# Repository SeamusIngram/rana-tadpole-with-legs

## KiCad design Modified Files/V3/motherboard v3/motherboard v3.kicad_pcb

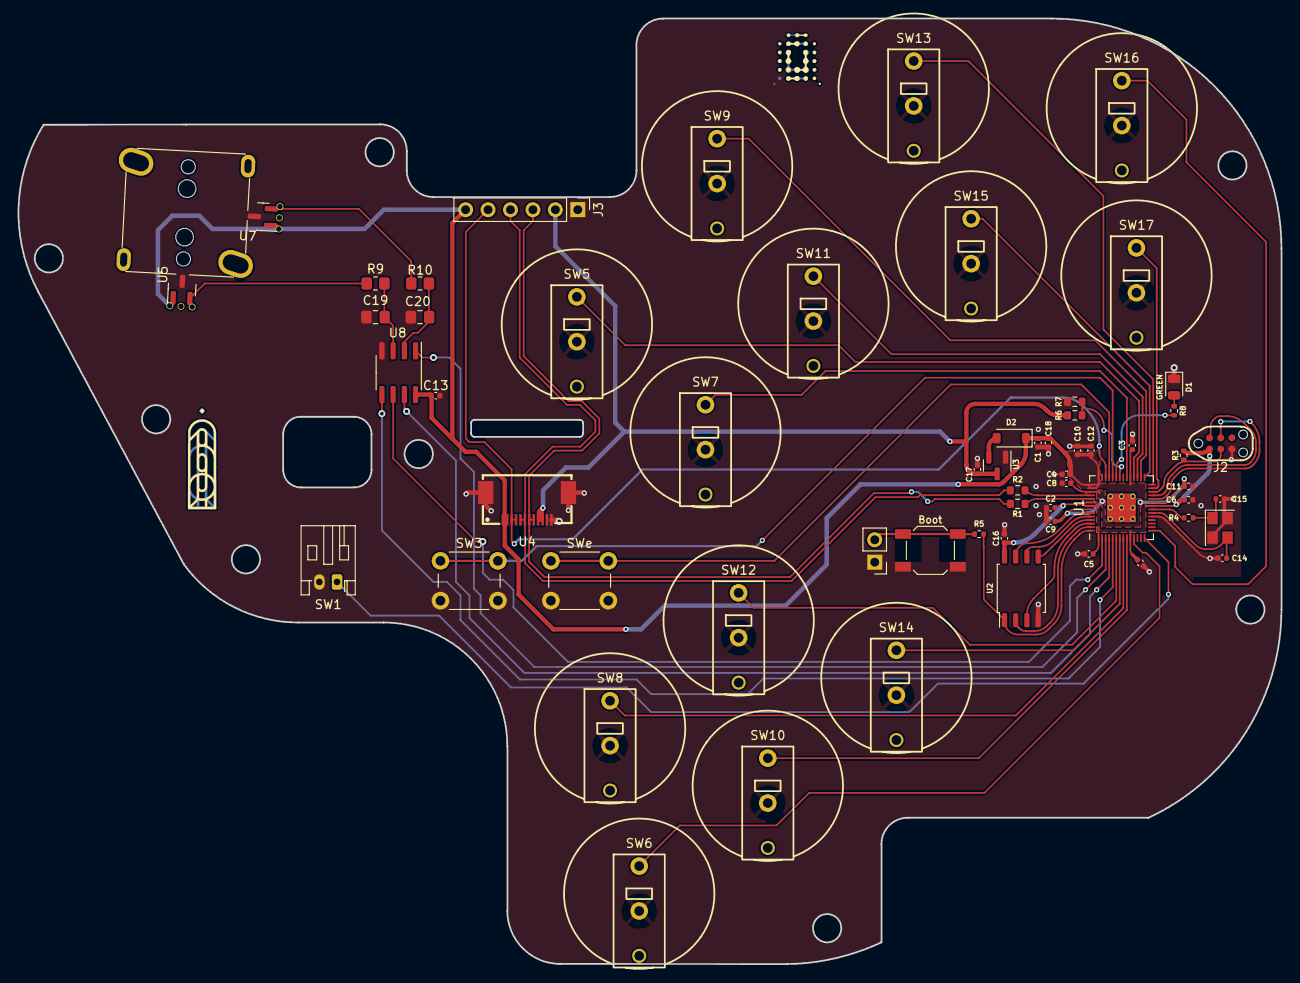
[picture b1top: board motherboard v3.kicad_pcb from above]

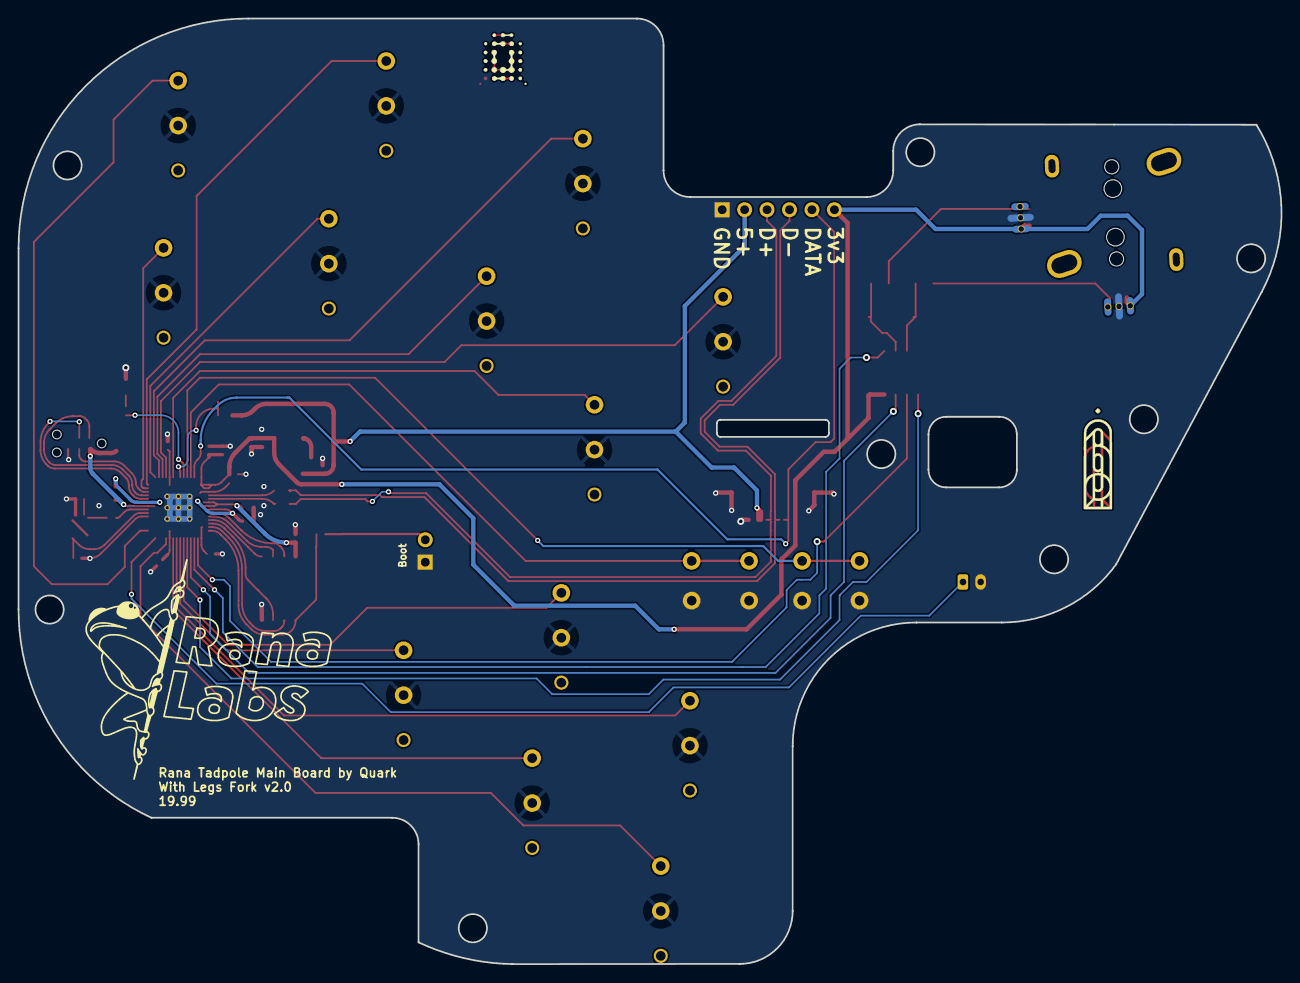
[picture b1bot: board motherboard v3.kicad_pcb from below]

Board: 2 copper layers, 142.9 x 107.0 mm, 65 parts (2 on the bottom side), 50 nets.

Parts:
C1: 10uF; C_0402_1005Metric
C2, C8, C17, C18: 1uF; C_0402_1005Metric
C3, C4, C5, C6, C7, C9, C10, C11, C12, C13, C16: 100nF; C_0402_1005Metric
C14, C15: 22pF; C_0402_1005Metric
C19, C20: 0.047u; C_0805_2012Metric_Pad1.18x1.45mm_HandSolder
D1: GREEN; LED_0805_2012Metric
D2: Schottky Diode; D_SOD-123
H1, H3: qw-logo; qw new logo silk + copper sm
H2, H4: 19.99 logo; 1999 logo md
J1: Conn_01x02; PinHeader_1x02_P2.54mm_Vertical
J2: JTAG_TC2030; CON_TC2030_outlined
J3: DuPont Connector; PinHeader_1x06_P2.54mm_Vertical
R1, R2: 27; R_0603_1608Metric
R3: 10k; R_0402_1005Metric
R4, R5: 1k; R_0402_1005Metric
R6: 5.6k; R_0603_1608Metric
R7: 10k; R_0603_1608Metric
R8: 470; R_0402_1005Metric
R9, R10: 2k; R_0805_2012Metric_Pad1.20x1.40mm_HandSolder
SW1: SW_Push; JST_PH_S2B-PH-K_1x02_P2.00mm_Horizontal
SW2: Boot; SW_SPST_SKQG_WithStem
SW3: SW_Push; SW_PUSH_6mm_H5mm
SW5, SW6, SW7, SW8, SW9, SW10, SW11, SW12, SW13, SW14, SW15, SW16, SW17: RanaTadpole
SWe: SW_Push; SW_PUSH_6mm_H5mm
U1: RP2040; RP2040-QFN-56
U2: W25Q128JVS; SOIC-8_5.23x5.23mm_P1.27mm
U3: XC6206; SOT-23
U4: X05A26H12G; FPC-SMD_X05A26H12G
U5, U7: DRV5055A2xDBZxQ1; SOT-23
U6: Stickbox_Assembly_CStick; GCC_Stickbox_Hall_Only
U8: MCP3002; SOIC-8_3.9x4.9mm_P1.27mm
Y1: 12MHz; Crystal_SMD_3225-4Pin_3.2x2.5mm

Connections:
3vDiode: C1.1, C2.1, C3.1, C4.1, C5.1, C6.1, C7.1, C10.1, C12.1, C13.1, C16.1, C18.2, D2.1 (K), J2.1 (VCC), J3.6, R3.1, U1.1 (IOVDD), U1.10 (IOVDD), U1.22 (IOVDD), U1.33 (IOVDD), U1.42 (IOVDD), U1.43 (ADC_AVDD), U1.44 (VREG_VIN), U1.48 (USB_VDD), U1.49 (IOVDD), U2.8 (VCC), U4.1, U4.2, U5.1 (VCC), U6.1 (H1XV), U6.4 (H1YV), U7.1 (VCC), U8.8 (VDD/VREF)
+1V1: C8.1, C9.1, C11.1, U1.23 (DVDD), U1.45 (VREG_VOUT), U1.50 (DVDD)
+5V: C17.2, J3.2, R6.1, U3.3 (VI), U4.9, U4.10
/D_+: R1.2, U1.47 (D+)
/D_-: R2.2, U1.46 (D-)
/XTAL_O: C15.2, R4.1, Y1.1
/~USB_BOOT: J1.2, R5.1, SW2.1
A: SW10.1, U1.9 (GPIO7)
B: SW7.1, U1.34 (GPIO22)
CLK: U1.4 (GPIO2), U8.7 (CLK)
CS: R5.2, U1.56 (QSPI_SS_N), U2.1 (~CS)
CS_SPI: U1.3 (GPIO1), U8.1 (~CS/SHDN)
C_DN: SW6.1, U1.11 (GPIO8)
C_LT: SW8.1, U1.8 (GPIO6)
C_RT: SW14.1, U1.7 (GPIO5)
C_UP: SW12.1, U1.6 (GPIO4)
D: SWe.1, U1.39 (GPIO27/ADC1)
D+: J3.3, R1.1, U4.7, U4.8
D-: J3.4, R2.1, U4.5, U4.6
DATA: J3.5, U1.40 (GPIO28/ADC2), U4.3, U4.4
GND: C1.2, C2.2, C3.2, C4.2, C5.2, C6.2, C7.2, C8.2, C9.2, C10.2, C11.2, C12.2, C13.2, C14.1, C15.1, C16.2, C17.1, C18.1, C19.2, C20.2, D1.1 (K), J1.1, J2.5 (GND), J3.1, R7.2, SW1.2, SW2.2, SW3.2, SW5.2, SW6.2, SW7.2, SW8.2, SW9.2, SW10.2, SW11.2, SW12.2, SW13.2, SW14.2, SW15.2, SW16.2, SW17.2, SWe.2, U1.19 (TESTEN), U1.57 (GND), U2.4 (GND), U3.1 (GND), U4.11, U4.12, U4.13, U4.14, U5.3 (GND), U6.2 (H1XG), U6.5 (H1YG), U7.3 (GND), U8.4 (VSS), Y1.2, Y1.4
L: SW1.1, U1.14 (GPIO11)
LS: SW13.1, U1.28 (GPIO17)
MOD: SW17.1, U1.27 (GPIO16)
MS: SW16.1, U1.15 (GPIO12)
unnamed: D1.2 (A), R8.2
unnamed: D2.2 (A), U3.2 (VO)
unnamed: C20.1, R10.2, U8.2 (CH0)
unnamed: C19.1, R9.2, U8.3 (CH1)
PICO_LED: R8.1, U1.37 (GPIO25)
QSPI_CLK: U1.52 (QSPI_SCLK), U2.6 (CLK)
R: SW5.1, U1.32 (GPIO21)
Rx: U1.2 (GPIO0), U8.6 (DOUT)
SD0: U1.53 (QSPI_SD0), U2.5 (DI(IO0))
SD1: U1.55 (QSPI_SD1), U2.2 (DO(IO1))
SD2: U1.54 (QSPI_SD2), U2.3 (IO2)
SD3: U1.51 (QSPI_SD3), U2.7 (IO3)
START: SW3.1, U1.38 (GPIO26/ADC0)
SWCLK: J2.4 (SWCLK), U1.24 (SWCLK)
SWD: J2.2 (SWDIO), U1.25 (SWDIO)
Tx: U1.5 (GPIO3), U8.5 (DIN)
VBUS_SENSE: R6.2, R7.1, U1.36 (GPIO24)
X: SW11.1, U1.31 (GPIO20)
XTAL_IN: C14.2, U1.20 (XTAL_IN), Y1.3
XTAL_OUT: R4.2, U1.21 (XTAL_OUT)
Y: SW9.1, U1.30 (GPIO19)
Z: SW15.1, U1.29 (GPIO18)
xHe: R9.1, U5.2 (OUT), U6.3 (H1XS)
yHe: R10.1, U6.6 (H1YS), U7.2 (OUT)
~RESET: J2.3 (~RST), R3.2, U1.26 (~RUN)

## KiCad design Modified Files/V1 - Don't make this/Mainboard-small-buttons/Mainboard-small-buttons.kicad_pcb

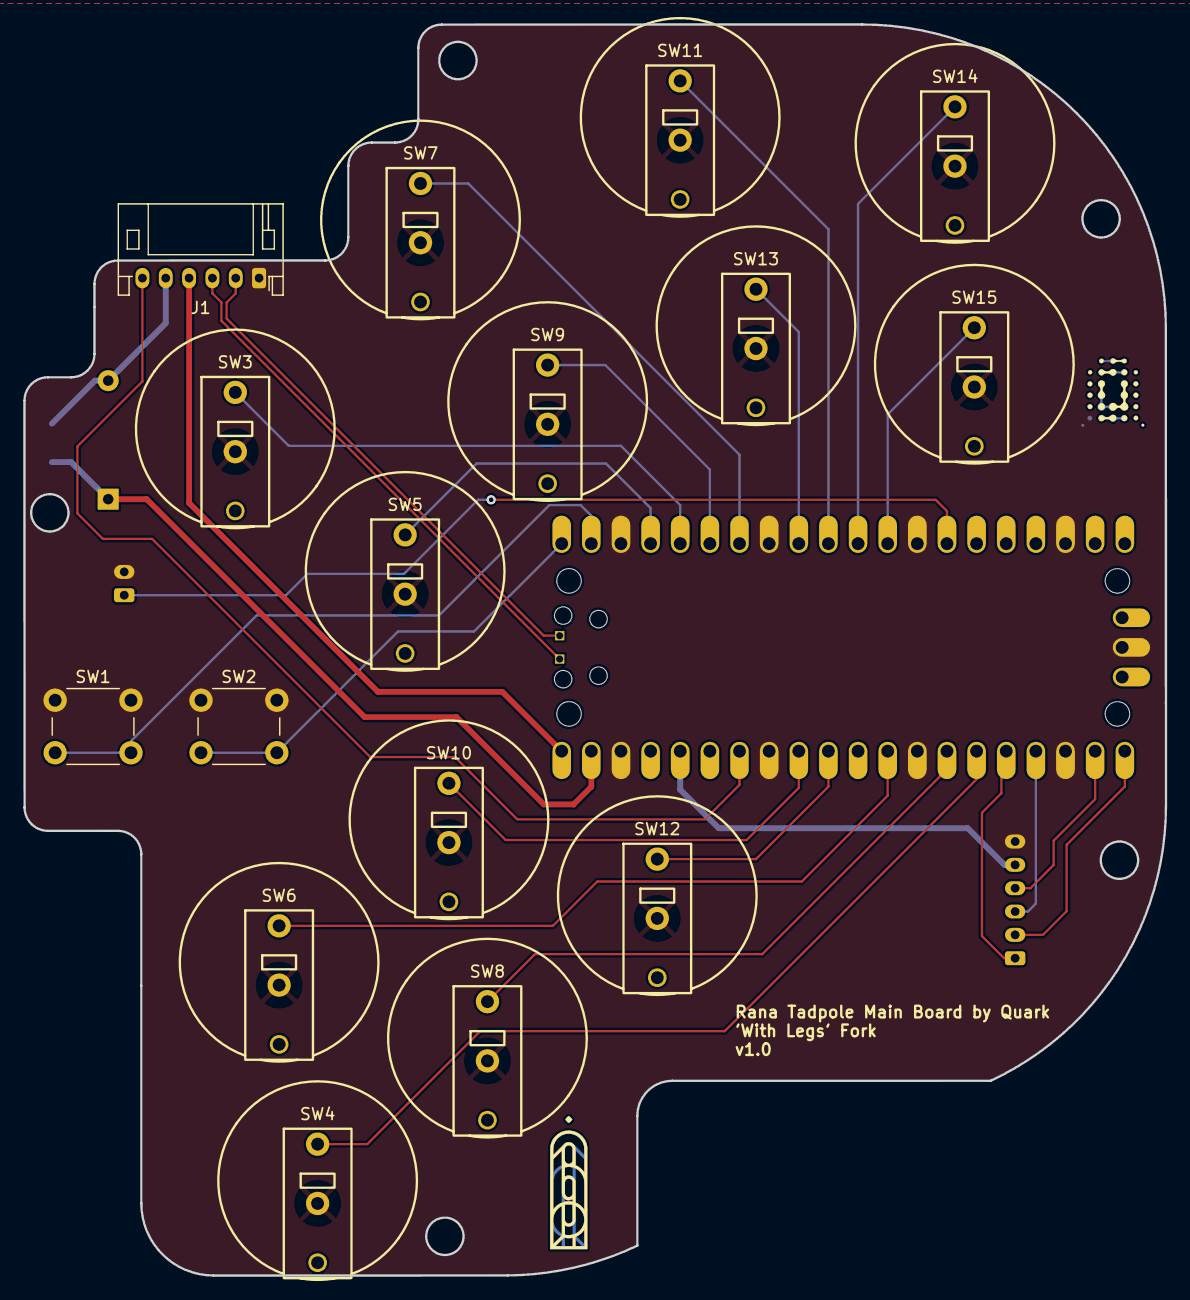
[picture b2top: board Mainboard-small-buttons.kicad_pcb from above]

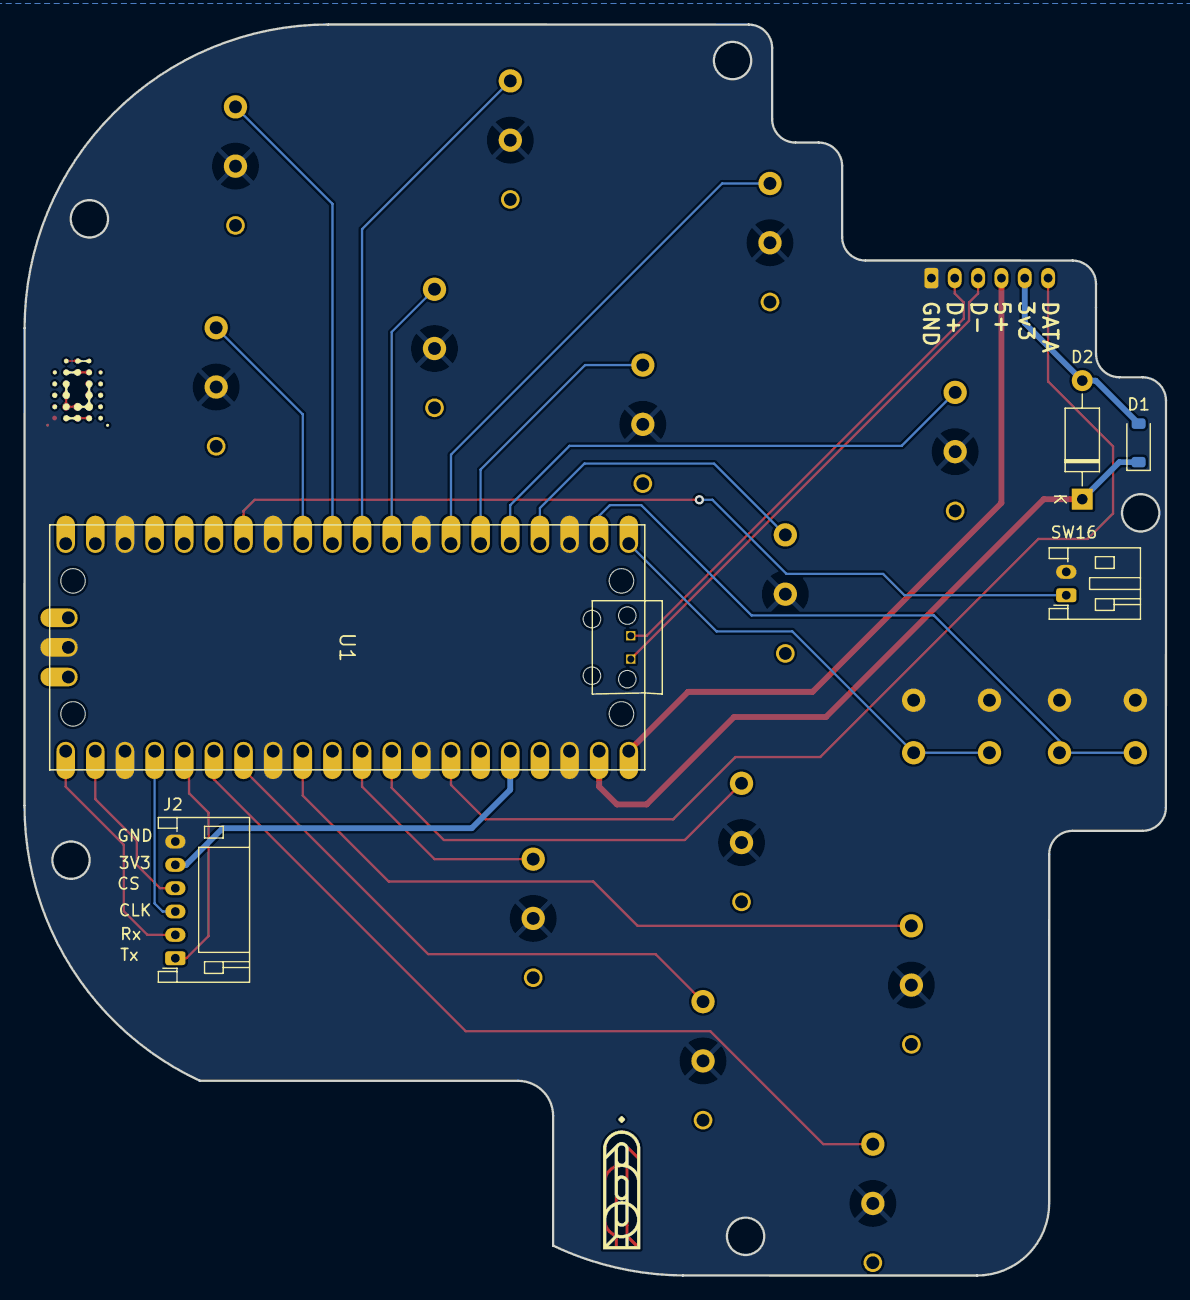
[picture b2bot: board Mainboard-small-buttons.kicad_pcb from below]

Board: 2 copper layers, 97.8 x 107.2 mm, 25 parts (7 on the bottom side), 28 nets.

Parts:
D1: Schottky Diode; D_SOD-123
D2: Schottky Diode; D_A-405_P10.16mm_Horizontal
H1, H3: qw-logo; qw new logo silk + copper sm
H2, H4: 19.99 logo; 1999 logo md
J1: I/O; JST_PH_S6B-PH-K_1x06_P2.00mm_Horizontal
J2: Analog Stick; JST_PH_S6B-PH-K_1x06_P2.00mm_Horizontal
SW1, SW2: SW_Push; SW_PUSH_6mm
SW3, SW4, SW5, SW6, SW7, SW8, SW9, SW10, SW11, SW12, SW13, SW14, SW15: RanaTadpole
SW16: SW_Push; JST_PH_S2B-PH-K_1x02_P2.00mm_Horizontal
U1: RPI_PICO-TH; RPI_PICO_TH

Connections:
3vDiode: D1.2 (A), D2.2 (A), J1.5
+3V3: J2.5, U1.3V3
+5V: J1.4, U1.VBUS
A: SW8.1, U1.GP21
B: SW5.1, U1.GP2
CLK: J2.3, U1.GP18
CS: J2.4, U1.GP17
C_DN: SW4.1, U1.GP20
C_LT: SW6.1, U1.GP22
C_RT: SW12.1, U1.GP26_A0
C_UP: SW10.1, U1.GP27_A1
D: SW2.2, U1.GP0
D+: J1.2, U1.TP3 (D+)
D-: J1.3, U1.TP2 (D-)
DATA: J1.6, U1.GP28_A2
EXTRA: SW16.1, U1.GP10
GND: J1.1, J2.6, SW1.1, SW2.1, SW3.2, SW4.2, SW5.2, SW6.2, SW7.2, SW8.2, SW9.2, SW10.2, SW11.2, SW12.2, SW13.2, SW14.2, SW15.2, SW16.2, U1.AGND, U1.GND@1 (GND), U1.GND@2 (GND), U1.GND@3 (GND), U1.GND@4 (GND), U1.GND@5 (GND), U1.GND@6 (GND), U1.GND@7 (GND), U1.GND@8 (GND)
LS: SW11.1, U1.GP7
MS: SW14.1, U1.GP8
R: SW3.1, U1.GP3
Rx: J2.2, U1.GP16
Start: SW1.2, U1.GP1
Tx: J2.1, U1.GP19
UP: SW15.1, U1.GP9
VSYS: D1.1 (K), D2.1 (K), U1.VSYS
X: SW9.1, U1.GP4
Y: SW7.1, U1.GP5
Z: SW13.1, U1.GP6

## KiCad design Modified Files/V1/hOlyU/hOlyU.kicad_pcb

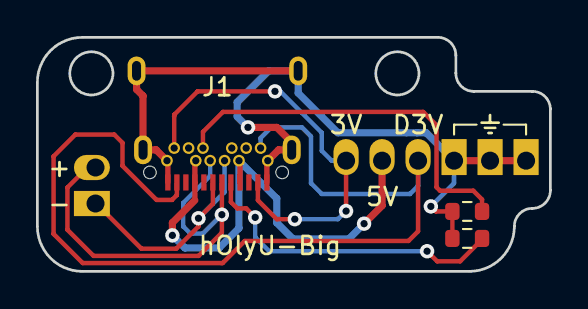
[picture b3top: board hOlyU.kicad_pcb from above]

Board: 2 copper layers, 28.5 x 13.0 mm, 5 parts (0 on the bottom side), 8 nets.

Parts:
J1: USB_C_Receptacle; Shou Han Type-C 24P QCHT
J2: Conn_01x06; PinHeader_1x06_P2.00mm_Vertical
J3: Conn_01x02; PinHeader_1x02_P2.00mm_Vertical
R1, R2: 5.1k; R_0603_1608Metric

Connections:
3V3: J1.A2, J1.B2, J2.1
D3V: J1.A11, J1.B11, J2.3
D+: J1.A6, J1.B6, J3.1
D-: J1.A7, J1.B7, J3.2
GND: J1.A1, J1.A12, J1.B1, J1.B12, J1.S1, J2.4, J2.5, J2.6, R1.1, R2.2
unnamed: J1.A5, R1.2
unnamed: J1.B5, R2.1
VBUS: J1.A4, J1.A9, J1.B4, J1.B9, J2.2

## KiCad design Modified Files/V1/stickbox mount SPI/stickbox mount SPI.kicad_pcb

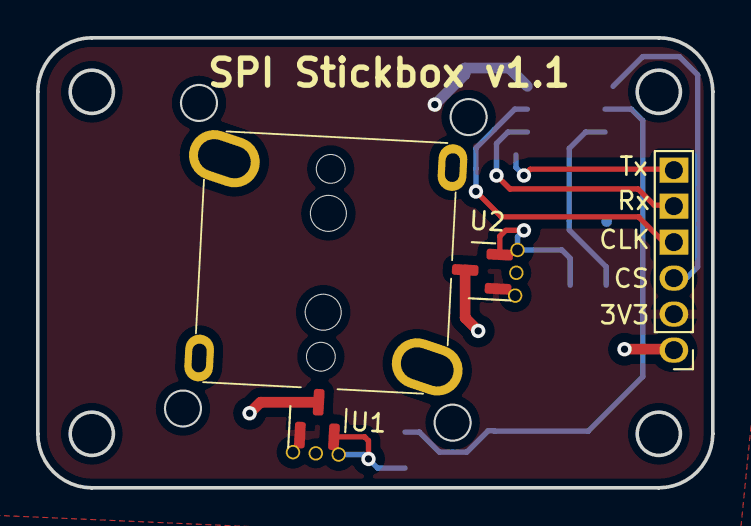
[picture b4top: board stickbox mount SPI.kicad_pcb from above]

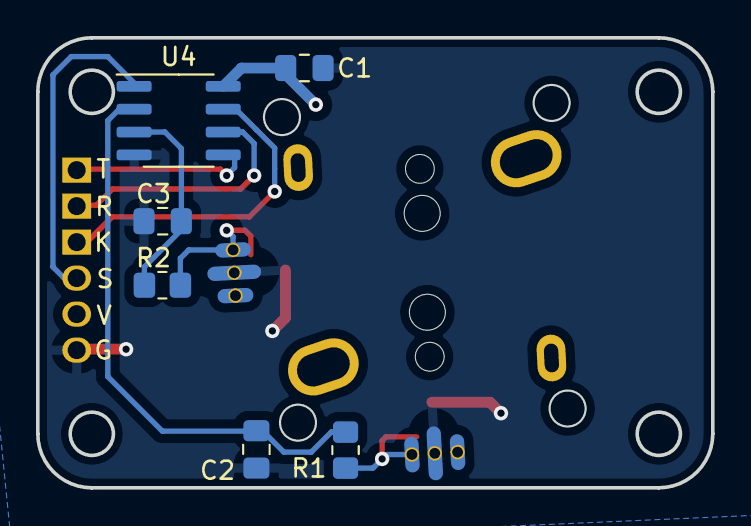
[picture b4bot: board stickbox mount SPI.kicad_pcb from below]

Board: 2 copper layers, 37.5 x 25.0 mm, 10 parts (6 on the bottom side), 10 nets.

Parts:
C1: 100n; C_0805_2012Metric_Pad1.18x1.45mm_HandSolder
C2, C3: 0.047u; C_0805_2012Metric_Pad1.18x1.45mm_HandSolder
J1: Conn_01x06_Female; GCC_Header_Straight_1x06_Pitch2.00mm
R1, R2: 2k; R_0805_2012Metric_Pad1.20x1.40mm_HandSolder
U1, U2: DRV5055A2xDBZxQ1; SOT-23
U3: Stickbox_Assembly_CStick; GCC_Stickbox_Hall_Only_Straps
U4: MCP3002; SOIC-8_3.9x4.9mm_P1.27mm

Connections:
/CLK: J1.4, U4.7 (CLK)
/CS: J1.3, U4.1 (~CS/SHDN)
/Rx: J1.5, U4.6 (DOUT)
/Tx: J1.6, U4.5 (DIN)
/xHE: R1.1, U1.2 (OUT), U3.3 (H1XS)
/yHE: R2.1, U2.2 (OUT), U3.6 (H1YS)
GND: C1.2, C2.2, C3.2, J1.1, U1.3 (GND), U2.3 (GND), U3.2 (H1XG), U3.5 (H1YG), U4.4 (VSS)
unnamed: C2.1, R1.2, U4.2 (CH0)
unnamed: C3.1, R2.2, U4.3 (CH1)
VCC: C1.1, J1.2, U1.1 (VCC), U2.1 (VCC), U3.1 (H1XV), U3.4 (H1YV), U4.8 (VDD/VREF)

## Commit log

2023-10-06 version 1
2023-11-24 Tadpole V1
2023-11-28 skipping v2 straight to v3
2023-12-28 V3/4 cad
